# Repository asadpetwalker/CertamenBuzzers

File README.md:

# CertamenBuzzers

A buzzer system for the game Certamen about Roman language, mythology, history, and culture. It is a quiz bowl style game, where whoever buzzes first gets a chance to claim the points.

# Why I made this

I made this because right now buzzer systems are inaccessible. Buzzer systems are sold by JCL, but they have a monopoly over it, so they mark up the prices incredibly even though the electronics are fairly simple, to 800 dollars. for the small version. I made this for my team, because they need a buzzer system to get practice in, since hyperbuzzing is an important strategy in more competitive leagues, as well as the fact that the current version is very bulky and you cannot bring it to places for practice.

# Wiring Diagram

Wire - Button - Wire

# Pictures

# BOM

| Name | Purpose | Cost | Qty | Total Cost | Link | Supplier |
|-----|-----|-----|-----|-----|-----|-----|
| GLF-464-144-521-D | Cables for Buzzers | $1.73 | 6 | $10.38 | https://www.digikey.com/en/products/detail/i-o-interconnect/GLF-464-144-521-D/773066 | DigiKey |
| 12 Buttons | Buzzers | $7.69 | 1 | $7.69 | https://www.amazon.com/MKBKLLJY-Latching-Button-Self-Locking-Terminal/dp/B0CPXMVL59 | Amazon |
| 27Ω Resistor | MCU | $0.01 | 10 | $0.06 | https://www.digikey.com/en/products/detail/yageo/RC0603FR-0727RL/727099 | DigiKey |
| 15pF Capacitor | Crystal Oscillator | $0.03 | 10 | $0.33 | https://www.digikey.com/en/products/detail/yageo/CC0603JRNPO9BN150/302794 | DigiKey |
| 1k Resistor | MCU | $0.01 | 10 | $0.06 | https://www.digikey.com/en/products/detail/stackpole-electronics-inc/RMCF0603FT1K00/1761077 | DigiKey |
| W25Q64JVZPIQ | Memory | $1.43 | 1 | $1.43 | https://www.digikey.com/en/products/detail/winbond-electronics/W25Q64JVZPIQ/15181953 | DigiKey |
| 10k Resistors | Buzzers | $0.00 | 25 | $0.12 | https://www.digikey.com/en/products/detail/stackpole-electronics-inc/RMCF0402FT10K0/1761433 | DigiKey |
| 12MHz Crystal | RP2040 | $0.45 | 1 | $0.45 | https://www.digikey.com/en/products/detail/abracon-llc/ABM10-166-12-000MHZ-T3/6140263 | DigiKey |
| RP2040 | MCU | $0.70 | 1 | $0.70 | https://www.digikey.com/en/products/detail/raspberry-pi/SC0914-13/14306010 | DigiKey |
| MTJ-662BX2 | Receptacle for cable buzzers | $0.21 | 12 | $2.56 | https://www.digikey.com/en/products/detail/adam-tech/MTJ-662BX2/9832250 | DigiKey |
| TVS1400 | Transient Suppression | $0.57 | 1 | $0.57 | https://www.digikey.com/en/products/detail/texas-instruments/TVS1400DRVR/8566097 | DigiKey |
| 100nF Capacitor | For RP2040 | $0.01 | 10 | $0.12 | https://www.digikey.com/en/products/detail/yageo/CC0805KRX7R9BB104/302874 | DigiKey |
| 10µF Capacitor | NCP117 | $0.02 | 10 | $0.16 | https://www.digikey.com/en/products/detail/taiyo-yuden/LMK212BJ106KG-T/930652 | DigiKey |
| KMR24 | Control Buttons | $0.67 | 2 | $1.34 | https://www.digikey.com/en/products/detail/c-k/KMR241NG-ULC-LFS/2043217 | DigiKey |
| USB4105 | USB For Programming MCU | $0.78 | 1 | $0.78 | https://www.digikey.com/en/products/detail/gct/USB4105-GF-A-120/14559037 | DigiKey |
| PS1240 | Buzzer for buzzing | $0.57 | 4 | $2.28 | https://www.digikey.com/en/products/detail/tdk-corporation/PS1240P02BT/935924 | DigiKey |
| NCP1117-3.3 | 3.3V LDO | $0.37 | 1 | $0.37 | https://www.digikey.com/en/products/detail/onsemi/NCP1117LPST33T3G/2194024 | DigiKey |
| PS102 | Button for resetting | $1.55 | 1 | $1.55 | https://www.digikey.com/en/products/detail/e-switch/PS1024ABLK/81742 | DigiKey |

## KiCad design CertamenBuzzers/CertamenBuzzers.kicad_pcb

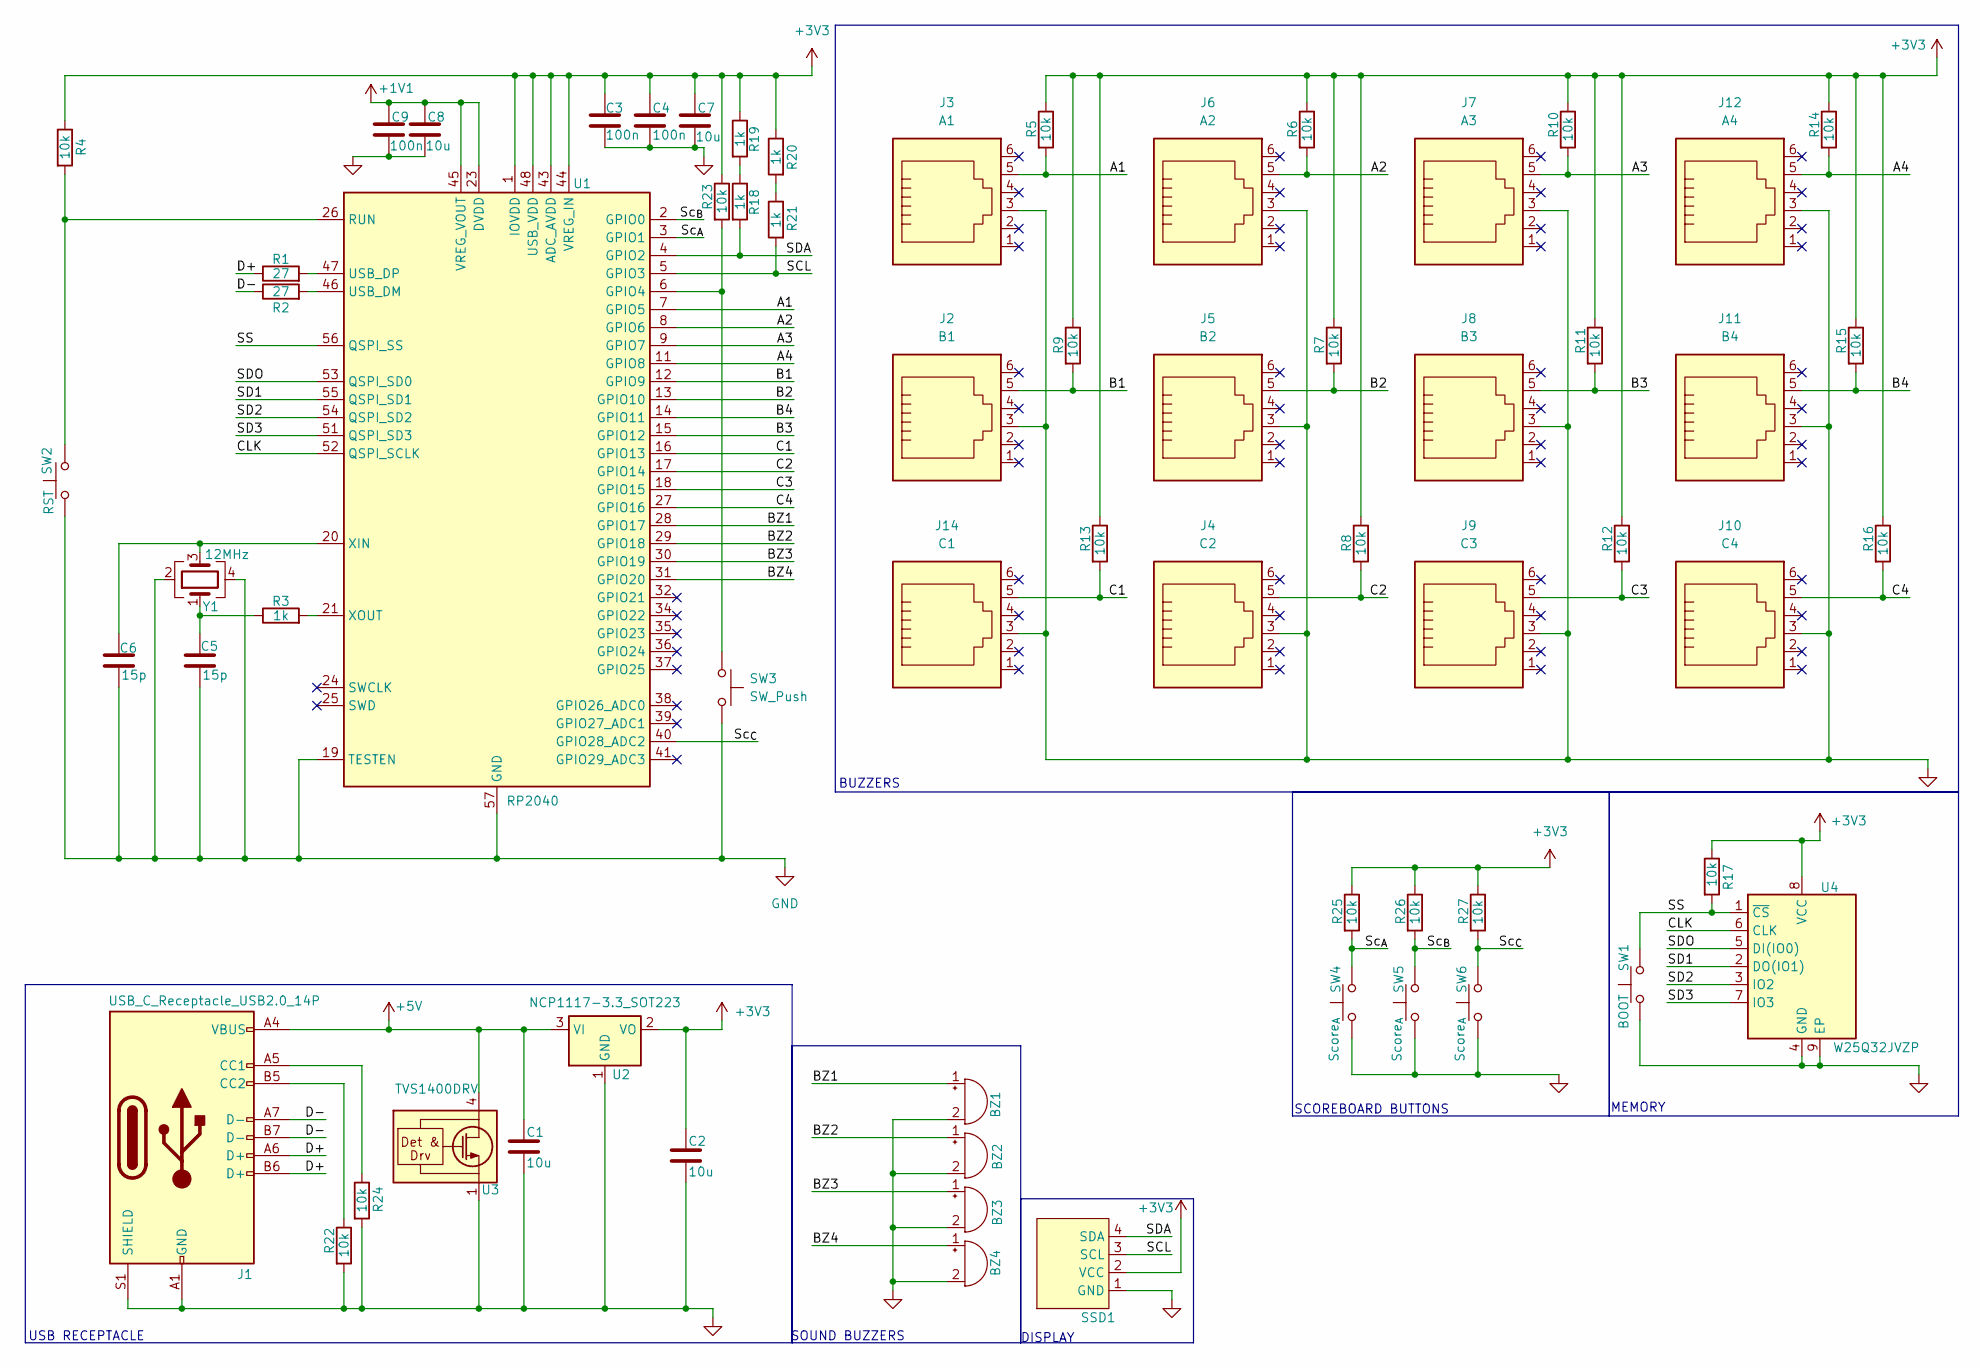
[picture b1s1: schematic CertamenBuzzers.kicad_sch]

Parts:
BZ1, BZ2, BZ3, BZ4: Buzzer; Buzzer_TDK_PS1240P02BT_D12.2mm_H6.5mm
C1, C2, C7, C8: 10u; C_0805_2012Metric
C3, C4, C9: 100n; C_0805_2012Metric
C5, C6: 15p; C_0603_1608Metric
J1: USB_C_Receptacle_USB2.0_14P; USB_C_Receptacle_GCT_USB4105-xx-A_16P_TopMnt_Horizontal
J2: B1; RJ25_Wayconn_MJEA-660X1_Horizontal
J3: A1; RJ25_Wayconn_MJEA-660X1_Horizontal
J4: C2; RJ25_Wayconn_MJEA-660X1_Horizontal
J5: B2; RJ25_Wayconn_MJEA-660X1_Horizontal
J6: A2; RJ25_Wayconn_MJEA-660X1_Horizontal
J7: A3; RJ25_Wayconn_MJEA-660X1_Horizontal
J8: B3; RJ25_Wayconn_MJEA-660X1_Horizontal
J9: C3; RJ25_Wayconn_MJEA-660X1_Horizontal
J10: C4; RJ25_Wayconn_MJEA-660X1_Horizontal
J11: B4; RJ25_Wayconn_MJEA-660X1_Horizontal
J12: A4; RJ25_Wayconn_MJEA-660X1_Horizontal
J14: C1; RJ25_Wayconn_MJEA-660X1_Horizontal
R1, R2: 27; R_0603_1608Metric
R3, R18, R19, R20, R21: 1k; R_0603_1608Metric
R4, R5, R6, R7, R8, R9, R10, R11, R12, R13, R14, R15, R16, R17, R22, R23, R24, R25, R26, R27: 10k; R_0603_1608Metric
SSD1: PinSocket_1x04_P2.54mm_Vertical
SW1: BOOT; SW_Push_1P1T_NO_CK_KMR2
SW2: RST; SW_Push_1P1T_NO_CK_KMR2
SW3: SW_Push; PinSocket_1x02_P2.54mm_Vertical
SW4, SW5, SW6: Score_{A}; PinSocket_1x02_P2.54mm_Vertical
U1: RP2040; QFN-56-1EP_7x7mm_P0.4mm_EP3.2x3.2mm
U2: NCP1117-3.3_SOT223; SOT-223-3_TabPin2
U3: TVS1400DRV; WSON-6-1EP_2x2mm_P0.65mm_EP1x1.6mm
U4: W25Q32JVZP; WSON-8-1EP_6x5mm_P1.27mm_EP3.4x4.3mm
Y1: 12MHz; Crystal_SMD_2520-4Pin_2.5x2.0mm

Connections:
+1V1: C8.1, C9.1, U1.23 (DVDD), U1.45 (VREG_VOUT), U1.50 (DVDD)
+3V3: C2.1, C3.1, C4.1, C7.1, R4.1, R5.1, R6.1, R7.1, R8.1, R9.1, R10.1, R11.1, R12.1, R13.1, R14.1, R15.1, R16.1, R17.1, R19.1, R20.1, R23.1, R25.1, R26.1, R27.1, SSD1.2 (VCC), U1.1 (IOVDD), U1.10 (IOVDD), U1.22 (IOVDD), U1.33 (IOVDD), U1.42 (IOVDD), U1.43 (ADC_AVDD), U1.44 (VREG_IN), U1.48 (USB_VDD), U1.49 (IOVDD), U2.2 (VO), U4.8 (VCC)
+5V: C1.1, J1.A4 (VBUS), J1.A9 (VBUS), J1.B4 (VBUS), J1.B9 (VBUS), U2.3 (VI), U3.4 (IN), U3.5 (IN), U3.6 (IN)
/A1: J3.5, R5.2, U1.7 (GPIO5)
/A2: J6.5, R6.2, U1.8 (GPIO6)
/A3: J7.5, R10.2, U1.9 (GPIO7)
/A4: J12.5, R14.2, U1.11 (GPIO8)
/B1: J2.5, R9.2, U1.12 (GPIO9)
/B2: J5.5, R7.2, U1.13 (GPIO10)
/B3: J8.5, R11.2, U1.15 (GPIO12)
/B4: J11.5, R15.2, U1.14 (GPIO11)
/BZ1: BZ1.1 (+), U1.28 (GPIO17)
/BZ2: BZ2.1 (+), U1.29 (GPIO18)
/BZ3: BZ3.1 (+), U1.30 (GPIO19)
/BZ4: BZ4.1 (+), U1.31 (GPIO20)
/C1: J14.5, R13.2, U1.16 (GPIO13)
/C2: J4.5, R8.2, U1.17 (GPIO14)
/C3: J9.5, R12.2, U1.18 (GPIO15)
/C4: J10.5, R16.2, U1.27 (GPIO16)
/CLK: U1.52 (QSPI_SCLK), U4.6 (CLK)
/D+: J1.A6 (D+), J1.B6 (D+), R1.1
/D-: J1.A7 (D-), J1.B7 (D-), R2.1
/SCL: R21.2, SSD1.3 (SCL), U1.5 (GPIO3)
/SD1: U1.55 (QSPI_SD1), U4.2 (DO(IO1))
/SD2: U1.54 (QSPI_SD2), U4.3 (IO2)
/SD3: U1.51 (QSPI_SD3), U4.7 (IO3)
/SDA: R18.2, SSD1.4 (SDA), U1.4 (GPIO2)
/SDO: U1.53 (QSPI_SD0), U4.5 (DI(IO0))
/SS: R17.2, SW1.2, U1.56 (QSPI_SS), U4.1 (~CS)
/Sc_{A}: R25.2, SW4.2, U1.3 (GPIO1)
/Sc_{B}: R26.2, SW5.2, U1.2 (GPIO0)
/Sc_{C}: R27.2, SW6.2, U1.40 (GPIO28_ADC2)
GND: BZ1.2 (-), BZ2.2 (-), BZ3.2 (-), BZ4.2 (-), C1.2, C2.2, C3.2, C4.2, C5.2, C6.2, C7.2, C8.2, C9.2, J1.A1 (GND), J1.A12 (GND), J1.B1 (GND), J1.B12 (GND), J1.S1 (SHIELD), J2.3, J3.3, J4.3, J5.3, J6.3, J7.3, J8.3, J9.3, J10.3, J11.3, J12.3, J14.3, R22.2, R24.2, SSD1.1 (GND), SW1.1, SW2.1, SW3.2, SW4.1, SW5.1, SW6.1, U1.19 (TESTEN), U1.57 (GND), U2.1 (GND), U3.1 (GND), U3.2 (GND), U3.3 (GND), U3.7 (GND), U4.4 (GND), U4.9 (EP), Y1.2, Y1.4
unnamed: C5.1, R3.1, Y1.1
unnamed: J1.A5 (CC1), R24.1
unnamed: J1.B5 (CC2), R22.1
unnamed: R18.1, R19.2
unnamed: R20.2, R21.1
unnamed: R23.2, SW3.1, U1.6 (GPIO4)
unnamed: R4.2, SW2.2, U1.26 (RUN)
unnamed: R2.2, U1.46 (USB_DM)
unnamed: R1.2, U1.47 (USB_DP)
unnamed: C6.1, U1.20 (XIN), Y1.3
unnamed: R3.2, U1.21 (XOUT)

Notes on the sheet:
SCOREBOARD BUTTONS
USB RECEPTACLE
SOUND BUZZERS
DISPLAY
BUZZERS
MEMORY

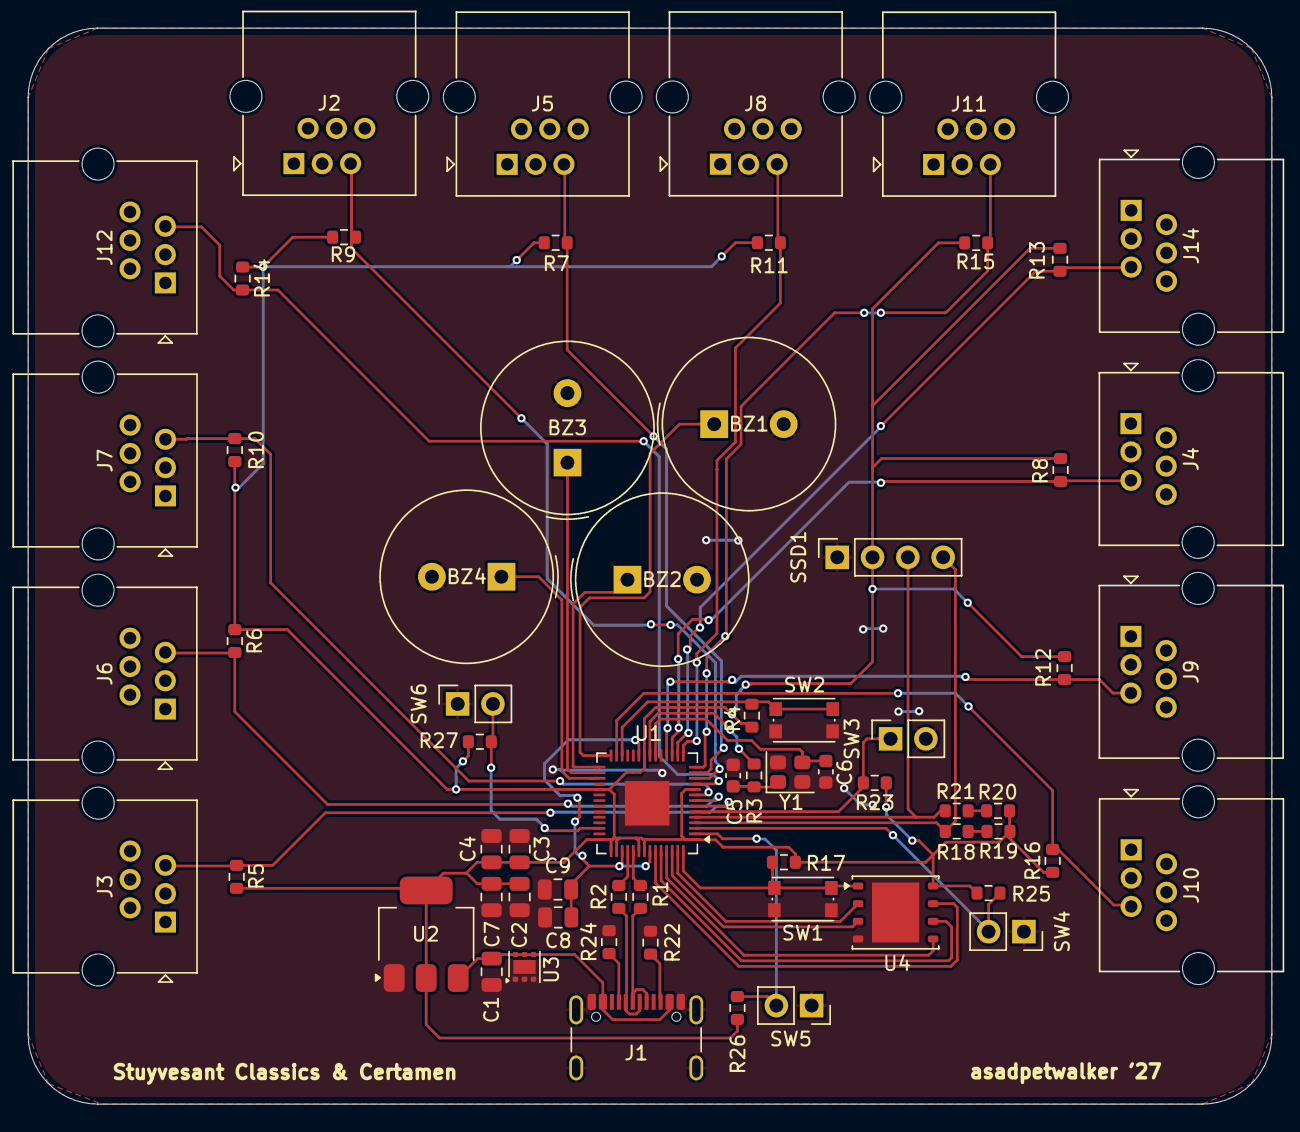
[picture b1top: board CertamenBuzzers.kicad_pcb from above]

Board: 2 copper layers, 89.5 x 77.4 mm, 65 parts (0 on the bottom side), 44 nets.

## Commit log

2026-03-06 Mostly done with schematic - need buzzers
2026-03-06 Schematic completed
2026-03-07 schematic cost optimized
2026-03-08 scheamtic done + cost optimized some more
2026-03-08 pcb done
2026-03-09 pcb done + receptacles adjusted + 3d models added
2026-03-13 pcb holes realigned
2026-03-14 Cad Done
2026-03-15 Code done
2026-03-15 readme
2026-03-16 buzzer buttons
2026-03-17 code button stuff
2026-03-17 source design file
2026-03-24 code
